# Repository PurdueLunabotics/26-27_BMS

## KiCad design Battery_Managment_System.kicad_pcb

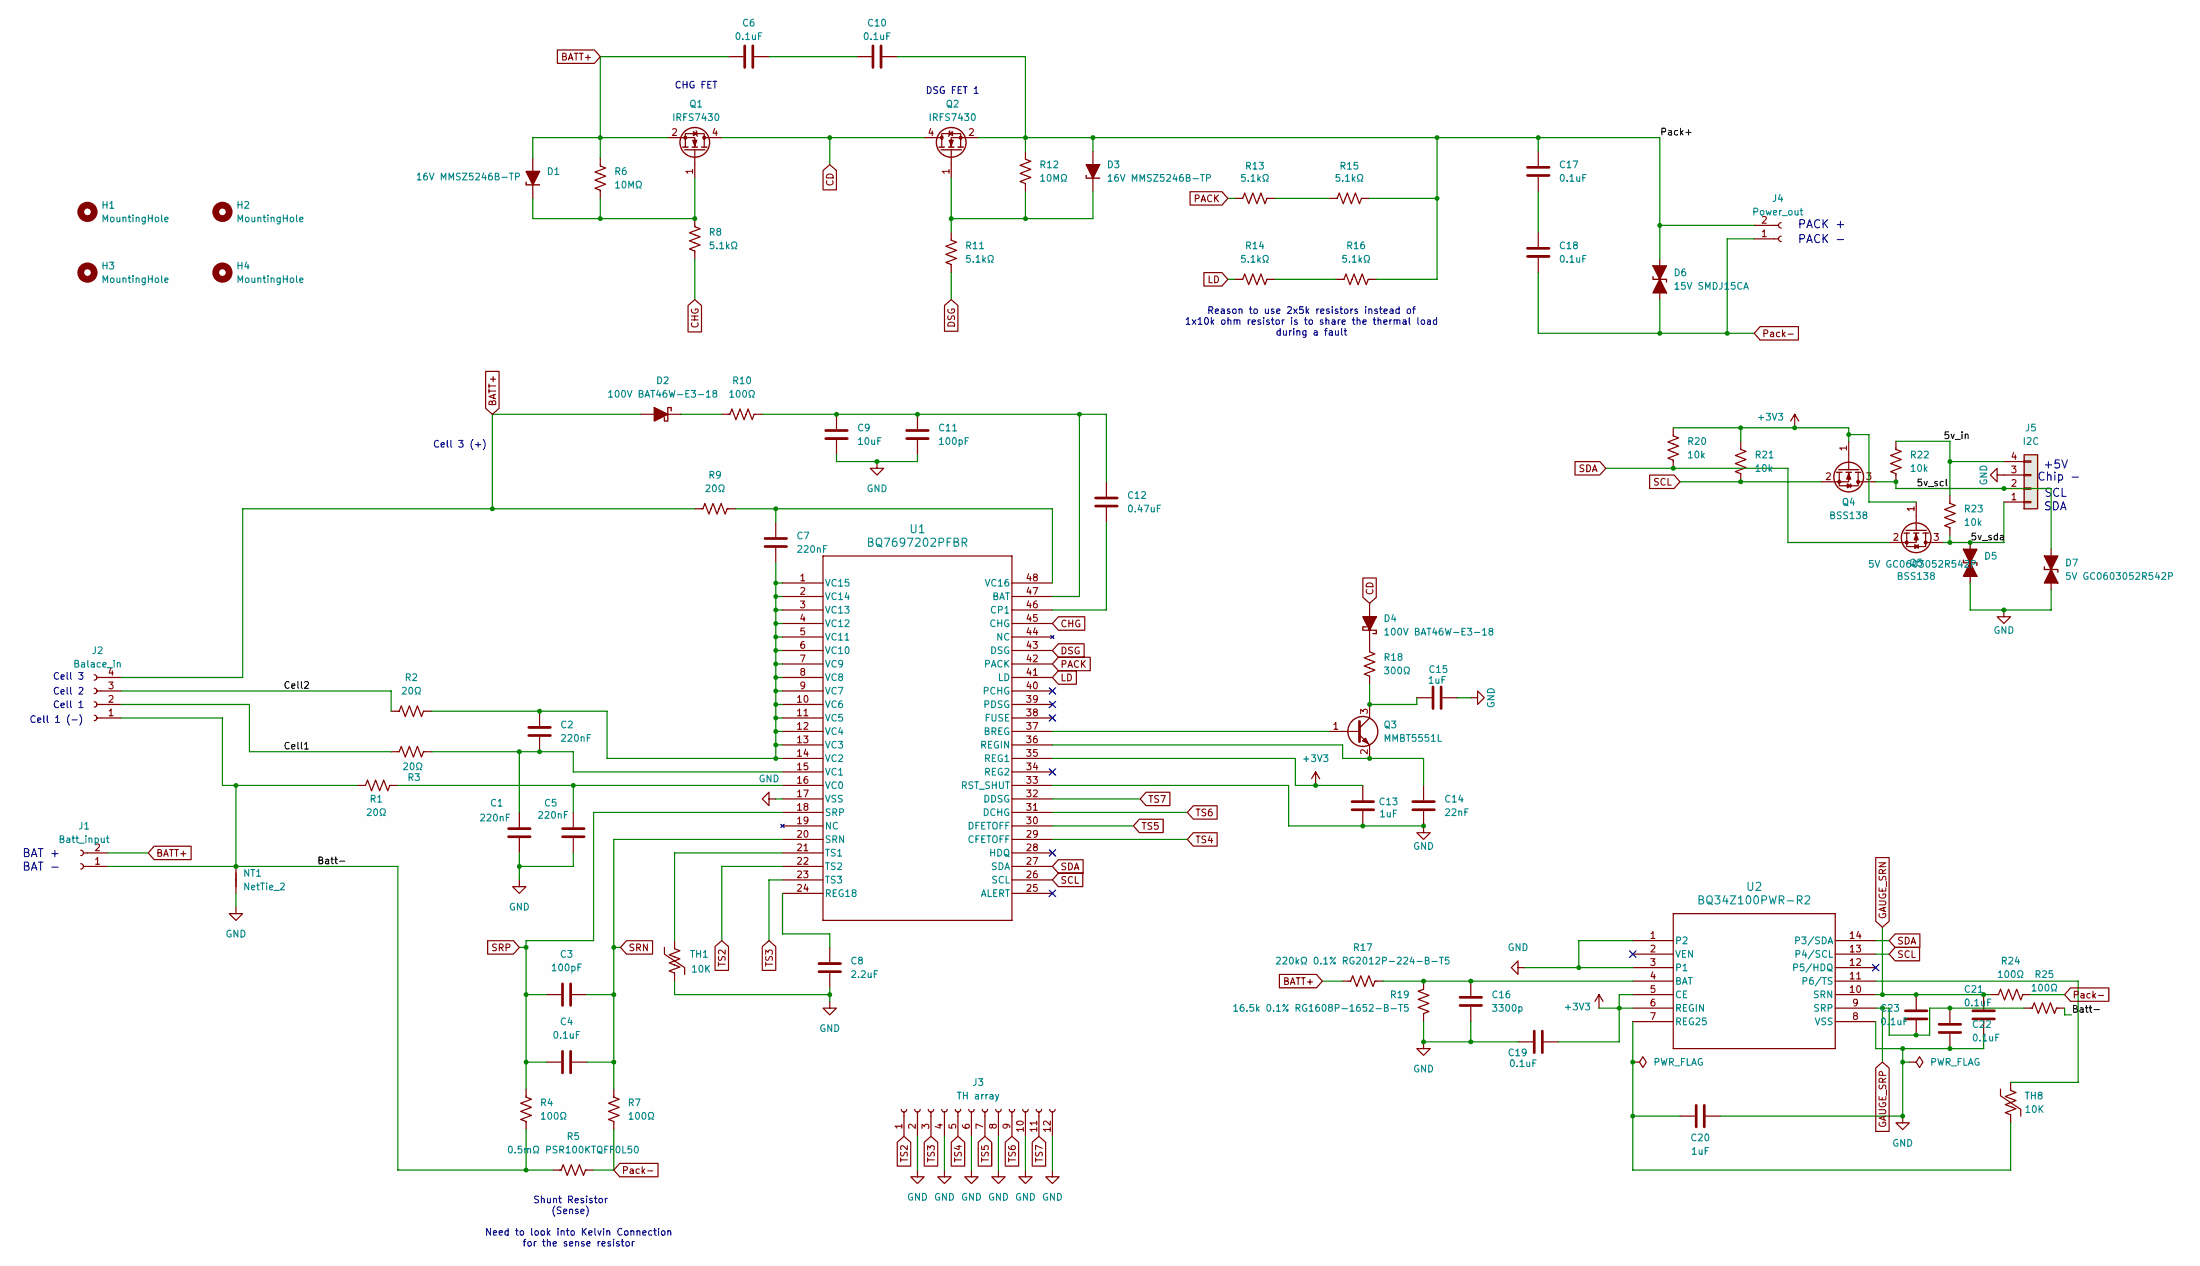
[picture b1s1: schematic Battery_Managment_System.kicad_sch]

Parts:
C1, C2, C5, C7: 220nF; C_0603_1608Metric; MPN CL10B224KB8NNNC
C3, C11: 100pF; C_0603_1608Metric; MPN C0603C101J1GACTU
C4, C6, C10, C17, C18, C21, C22, C23: 0.1uF; C_0805_2012Metric; MPN C2012X7R2A104K125AA
C8: 2.2uF; C_0603_1608Metric; MPN GRT188R61H225KE13D
C9: 10uF; C_0805_2012Metric; MPN GMC21X5R106K35NT
C12: 0.47uF; C_0603_1608Metric; MPN UMK107B7474KA-TR
C13, C15: 1uF; C_0603_1608Metric; MPN GRM188R71E105KA12D
C14: 22nF; C_0603_1608Metric; MPN CGA3E2X7R1H223K080AA
C16: 3300p; C_0603_1608Metric; MPN CL10B332KB8NNNC
C19: 0.1uF; C_0805_2012Metric; Voltage 10V; MPN C2012X7R2A104K125AA
C20: 1uF; C_0603_1608Metric; Voltage 10V; MPN GRM188R71E105KA12D
D1, D3: 16V MMSZ5246B-TP; D_SOD-123; MPN MMSZ5246B-TP
D2, D4: 100V BAT46W-E3-18; D_SOD-123; MPN BAT46W-E3-18
D5, D7: 5V GC0603052R542P; D_0603_1608Metric; MPN GC0603052R542P
D6: 15V SMDJ15CA; D_SMC; MPN SMDJ15CA
H1, H2, H3, H4: MountingHole; MountingHole_2.2mm_M2_DIN965_Pad_TopBottom
J1: Batt_input; TH_XT90PB-F; MPN XT90PB-M
J2: Balace_in; JST_XH_B4B-XH-A_1x04_P2.50mm_Vertical; MPN B4B-XH-A
J3: TH array; JST_XH_B12B-XH-A_1x12_P2.50mm_Vertical; MPN B12B-XH-A
J4: Power_out; XT90PWF; MPN XT90PW-F
J5: I2C; JST_XH_B4B-XH-A_1x04_P2.50mm_Vertical; MPN B4B-XH-A
NT1: NetTie_2; NetTie-2_SMD_Pad2.0mm
Q1, Q2: IRFS7430; TO-263-6; MPN IRFS7430TRL7PP
Q3: MMBT5551L; SOT-23; MPN MMBT5551L
Q4, Q5: BSS138; SOT-23; MPN BSS138-D
R1, R2, R3, R9: 20Ω; R_0603_1608Metric; MPN RCS060320R0FKEA
R4, R7, R10, R24, R25: 100Ω; R_0603_1608Metric; MPN SG73P1JTTD1000F
R5: 0.5mΩ PSR100KTQFF0L50; R_2512_6332Metric; MPN PSR100KTQFF0L50
R6, R12: 10MΩ; R_0603_1608Metric; MPN RCS060310M0FKEA
R8, R11, R13, R14, R15, R16: 5.1kΩ; R_0603_1608Metric; MPN RCS06035K10FKEA
R17: 220kΩ 0.1% RG2012P-224-B-T5; R_0805_2012Metric; Tolerance 0.1% 25ppm; MPN RG2012P-224-B-T5
R18: 300Ω; R_0603_1608Metric; MPN RCS0603300RFKEA
R19: 16.5k 0.1% RG1608P-1652-B-T5; R_0603_1608Metric; Tolerance 0.1% 25ppm; MPN RG1608P-1652-B-T5
R20, R21, R22, R23: 10k; R_0603_1608Metric; MPN SG73P1JTTD1002F
TH1, TH8: 10K; C_Disc_D3.0mm_W1.6mm_P2.50mm; MPN 103AT-2
U1: BQ7697202PFBR; TQFP-48_7x7mm_P0.5mm; MPN BQ7697202PFBR
U2: BQ34Z100PWR-R2; TSSOP-14_4.4x5mm_P0.65mm; MPN BQ34Z100PWR-R2

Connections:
+3V3: C13.1, C19.1, Q4.1 (G), Q5.1 (G), R20.2, R21.2, U1.35 (REG1), U2.5 (CE), U2.6 (REGIN)
/5v_in: J5.4, R22.2, R23.2
/5v_scl: D7.2 (A2), J5.2, Q4.3 (D), R22.1
/5v_sda: D5.2 (A2), J5.1, Q5.3 (D), R23.1
/Batt-: J1.1, J2.1, NT1.2, R1.2, R4.2, R5.1, R25.2
/Cell1: J2.2, R3.1
/Cell2: J2.3, R2.1
/Pack+: C10.2, C17.1, D3.2 (A), D6.2 (A2), J4.2, Q2.2 (S), Q2.3 (S), Q2.5 (S), Q2.6 (S), Q2.7 (S), R12.1, R15.2, R16.2
BATT+: C6.1, D1.2 (A), D2.2 (A), J1.2, J2.4, Q1.2 (S), Q1.3 (S), Q1.5 (S), Q1.6 (S), Q1.7 (S), R6.1, R9.1, R17.1
CD: D4.2 (A), Q1.4 (D), Q2.4 (D)
CHG: R8.2, U1.45 (CHG)
DSG: R11.2, U1.43 (DSG)
GAUGE_SRN: C21.2, C23.2, R24.1, U2.10 (SRN)
GAUGE_SRP: C22.2, C23.1, R25.1, U2.9 (SRP)
GND: C1.1, C5.1, C8.2, C9.2, C11.2, C13.2, C14.2, C15.2, C16.2, C19.2, C20.2, C21.1, C22.1, D5.1 (A1), D7.1 (A1), J3.2, J3.4, J3.6, J3.8, J3.10, J3.12, J5.3, NT1.1, R19.2, TH1.2, U1.17 (VSS), U1.33 (RST_SHUT), U2.1 (P2), U2.3 (P1), U2.8 (VSS)
LD: R14.1, U1.41 (LD)
unnamed: C6.2, C10.1
unnamed: C17.2, C18.1
unnamed: D1.1 (K), Q1.1 (G), R6.2, R8.1
unnamed: D2.1 (K), R10.1
unnamed: D3.1 (K), Q2.1 (G), R11.1, R12.2
unnamed: D4.1 (K), R18.2
unnamed: Q3.1 (B), U1.37 (BREG)
unnamed: C15.1, Q3.3 (C), R18.1
unnamed: C14.1, Q3.2 (E), U1.36 (REGIN)
unnamed: R13.2, R15.1
unnamed: R14.2, R16.1
unnamed: C9.1, C11.1, C12.1, R10.2, U1.47 (BAT)
unnamed: C12.2, U1.46 (CP1)
unnamed: C8.1, U1.24 (REG18)
unnamed: TH1.1, U1.21 (TS1)
unnamed: C5.2, R1.1, U1.16 (VC0)
unnamed: C1.2, C2.2, R3.2, U1.15 (VC1)
unnamed: C2.1, C7.1, R2.2, U1.1 (VC15), U1.2 (VC14), U1.3 (VC13), U1.4 (VC12), U1.5 (VC11), U1.6 (VC10), U1.7 (VC9), U1.8 (VC8), U1.9 (VC7), U1.10 (VC6), U1.11 (VC5), U1.12 (VC4), U1.13 (VC3), U1.14 (VC2)
unnamed: C7.2, R9.2, U1.48 (VC16)
unnamed: C16.1, R17.2, R19.1, U2.4 (BAT)
unnamed: TH8.2, U2.11 (P6/TS)
unnamed: C20.1, TH8.1, U2.7 (REG25)
PACK: R13.1, U1.42 (PACK)
Pack-: C18.2, D6.1 (A1), J4.1, R5.2, R7.2, R24.2
SCL: Q4.2 (S), R21.1, U1.26 (SCL), U2.13 (P4/SCL)
SDA: Q5.2 (S), R20.1, U1.27 (SDA), U2.14 (P3/SDA)
SRN: C3.2, C4.2, R7.1, U1.20 (SRN)
SRP: C3.1, C4.1, R4.1, U1.18 (SRP)
TS2: J3.1, U1.22 (TS2)
TS3: J3.3, U1.23 (TS3)
TS4: J3.5, U1.29 (CFETOFF)
TS5: J3.7, U1.30 (DFETOFF)
TS6: J3.9, U1.31 (DCHG)
TS7: J3.11, U1.32 (DDSG)

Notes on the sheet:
Reason to use 2x5k resistors instead of 1x10k ohm resistor is to share the thermal load during a fault
PACK -
Need to look into Kelvin Connection for the sense resistor
DSG FET 1
Chip -
CHG FET
Cell 1
BAT +
Cell 3 (+)
+5V
BAT -
PACK +
Shunt Resistor (Sense)
Cell 2
Cell 1 (-)
Cell 3
SCL
SDA

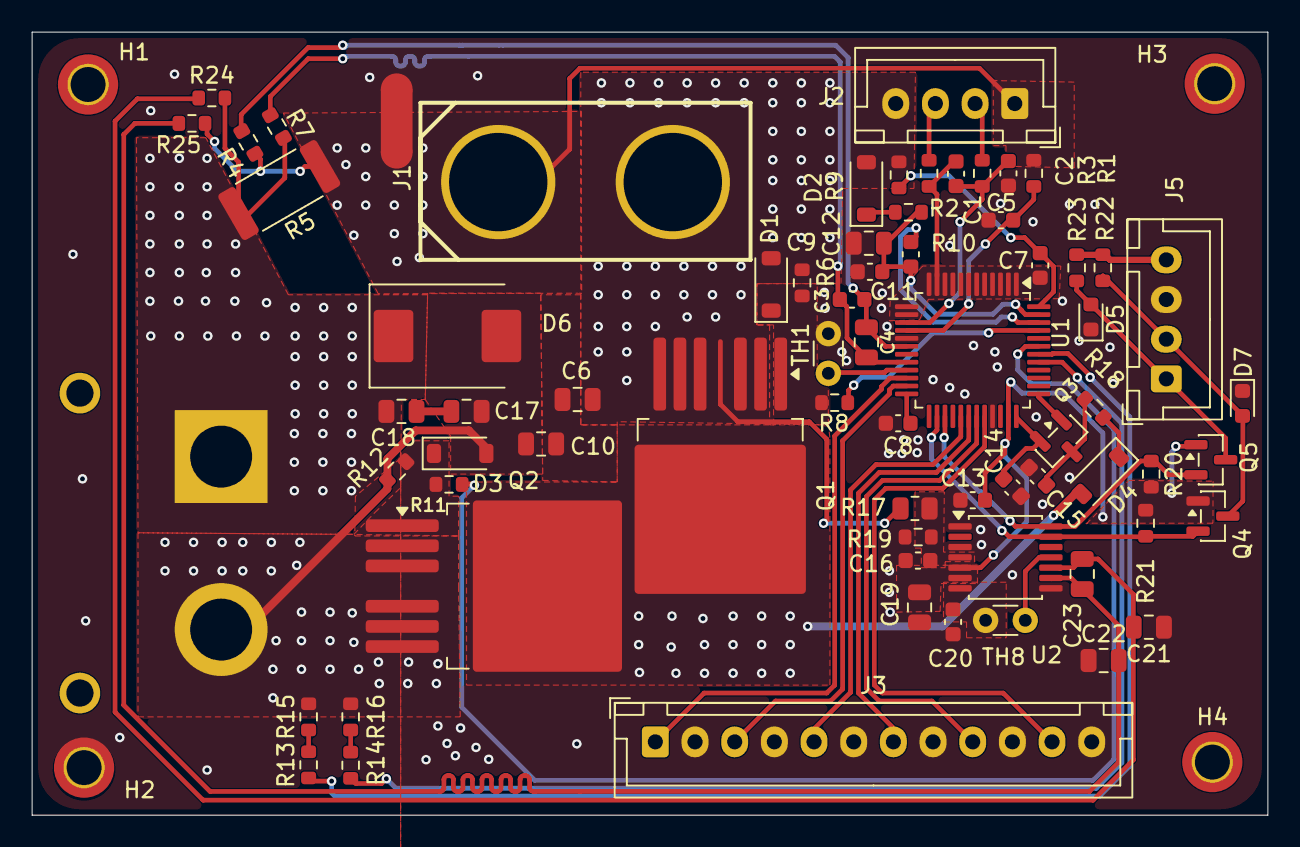
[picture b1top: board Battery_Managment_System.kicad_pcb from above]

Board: 2 copper layers, 77.9 x 49.4 mm, 74 parts (1 on the bottom side), 50 nets.

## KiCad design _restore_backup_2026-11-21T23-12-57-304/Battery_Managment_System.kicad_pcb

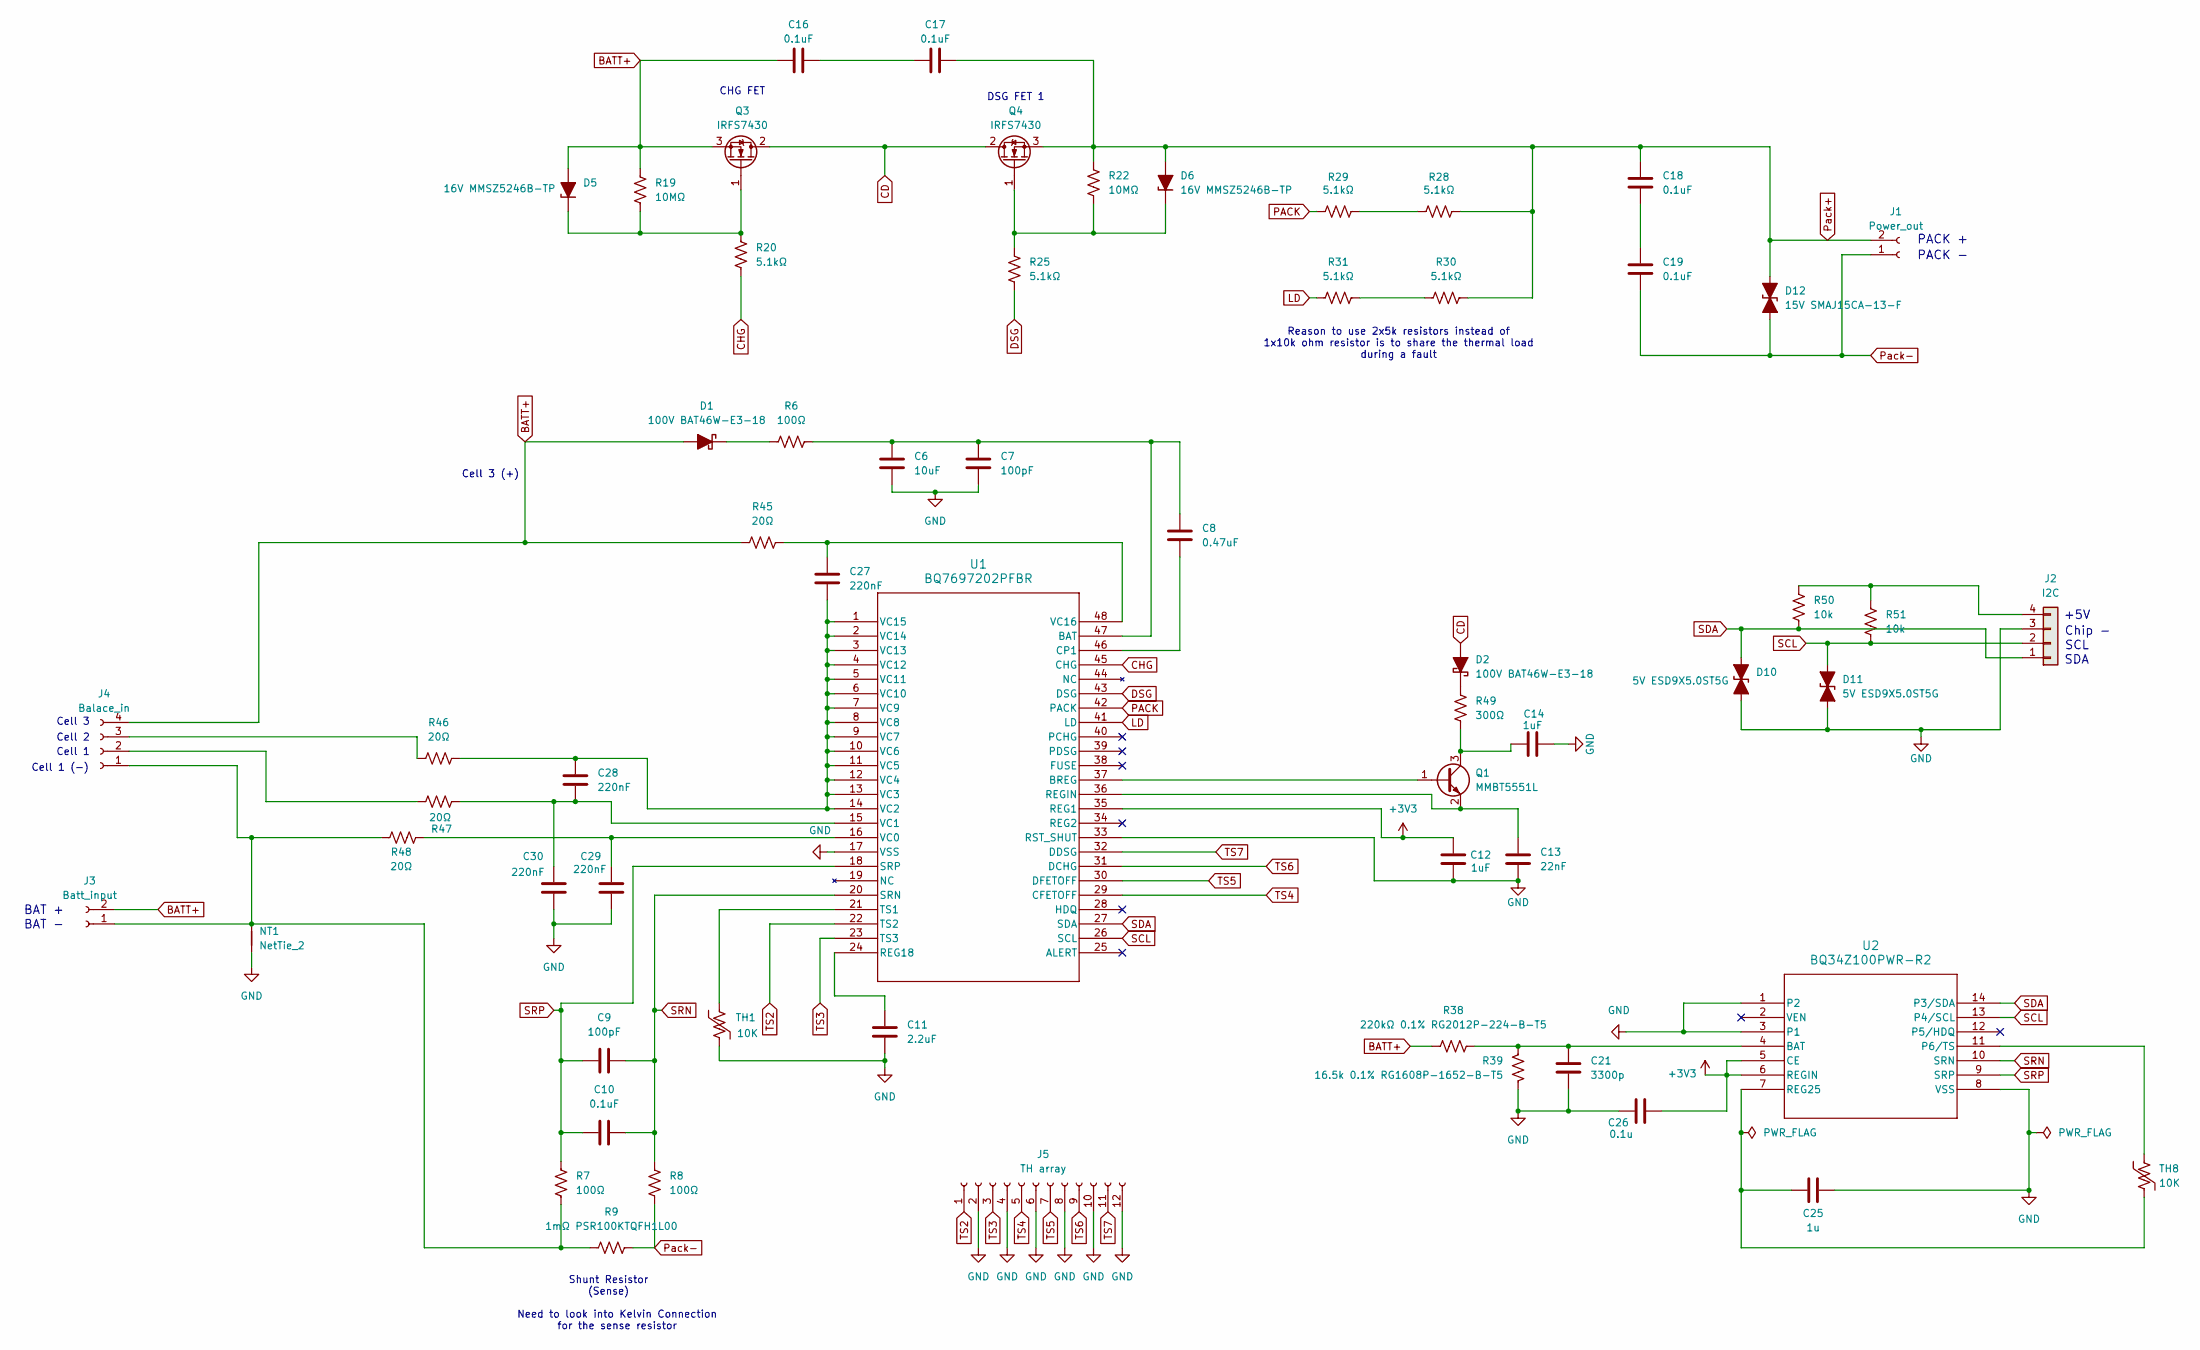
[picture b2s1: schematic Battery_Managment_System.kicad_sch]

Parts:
C6: 10uF; C_0805_2012Metric
C7, C9: 100pF; C_0402_1005Metric
C8: 0.47uF; C_0402_1005Metric
C10: 0.1uF; C_0402_1005Metric
C11: 2.2uF; C_0603_1608Metric
C12, C14: 1uF; C_0603_1608Metric
C13: 22nF; C_0402_1005Metric
C16, C17, C18, C19: 0.1uF; C_0805_2012Metric
C21: 3300p; C_0402_1005Metric
C25: 1u; C_0603_1608Metric; Voltage 10V
C26: 0.1u; C_0402_1005Metric; Voltage 10V
C27, C28, C29, C30: 220nF; C_0402_1005Metric
D1, D2: 100V BAT46W-E3-18; D_SOD-123
D5, D6: 16V MMSZ5246B-TP; D_SOD-123
D10, D11: 5V ESD9X5.0ST5G; D_SOD-923
D12: 15V SMAJ15CA-13-F; D_SMA
J1: Power_out; XT90PWF
J2: I2C; JST_XH_B4B-XH-A_1x04_P2.50mm_Vertical
J3: Batt_input; TH_XT90PB-F
J4: Balace_in; JST_XH_B4B-XH-A_1x04_P2.50mm_Vertical
J5: TH array; JST_XH_B12B-XH-A_1x12_P2.50mm_Vertical
NT1: NetTie_2; NetTie-2_SMD_Pad2.0mm
Q1: MMBT5551L; SOT-23
Q3, Q4: IRFS7430; TO-263-2
R6, R7, R8: 100Ω; R_0402_1005Metric
R9: 1mΩ PSR100KTQFH1L00; R_2512_6332Metric
R19, R22: 10MΩ; R_0402_1005Metric
R20, R25, R28, R29, R30, R31: 5.1kΩ; R_0402_1005Metric
R38: 220kΩ 0.1% RG2012P-224-B-T5; R_0805_2012Metric; Tolerance 0.1% 25ppm
R39: 16.5k 0.1% RG1608P-1652-B-T5; R_0603_1608Metric; Tolerance 0.1% 25ppm
R45, R46, R47, R48: 20Ω; R_0402_1005Metric
R49: 300Ω; R_0402_1005Metric
R50, R51: 10k; R_0402_1005Metric
TH1: 10K; C_Disc_D3.0mm_W1.6mm_P2.50mm
TH8: 10K; C_Disc_D3.0mm_W1.6mm_P2.50mm; MPN Semitec 103AT-2
U1: BQ7697202PFBR; TQFP-48_7x7mm_P0.5mm
U2: BQ34Z100PWR-R2; TSSOP-14_4.4x5mm_P0.65mm; MPN BQ34Z100PWR-R2

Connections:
+3V3: C12.1, C26.1, U1.35 (REG1), U2.5 (CE), U2.6 (REGIN)
BATT+: C16.1, D1.2 (A), D5.2 (A), J3.2, J4.4, Q3.3 (S), R19.1, R38.1, R45.1
CD: D2.2 (A), Q3.2 (D), Q4.2 (D)
CHG: R20.2, U1.45 (CHG)
DSG: R25.2, U1.43 (DSG)
GND: C6.2, C7.2, C11.2, C12.2, C13.2, C14.2, C21.2, C25.2, C26.2, C29.1, C30.1, D10.1 (A1), D11.1 (A1), J2.3, J5.2, J5.4, J5.6, J5.8, J5.10, J5.12, NT1.1, R39.2, TH1.2, U1.17 (VSS), U1.33 (RST_SHUT), U2.1 (P2), U2.3 (P1), U2.8 (VSS)
LD: R31.1, U1.41 (LD)
unnamed: C16.2, C17.1
unnamed: C18.2, C19.1
unnamed: D1.1 (K), R6.1
unnamed: D2.1 (K), R49.2
unnamed: D5.1 (K), Q3.1 (G), R19.2, R20.1
unnamed: D6.1 (K), Q4.1 (G), R22.2, R25.1
unnamed: J2.4, R50.2, R51.2
unnamed: J3.1, J4.1, NT1.2, R7.2, R9.1, R48.2
unnamed: J4.2, R47.1
unnamed: J4.3, R46.1
unnamed: Q1.1 (B), U1.37 (BREG)
unnamed: C14.1, Q1.3 (C), R49.1
unnamed: C13.1, Q1.2 (E), U1.36 (REGIN)
unnamed: R28.1, R29.2
unnamed: R30.1, R31.2
unnamed: C6.1, C7.1, C8.1, R6.2, U1.47 (BAT)
unnamed: C8.2, U1.46 (CP1)
unnamed: C11.1, U1.24 (REG18)
unnamed: TH1.1, U1.21 (TS1)
unnamed: C29.2, R48.1, U1.16 (VC0)
unnamed: C28.2, C30.2, R47.2, U1.15 (VC1)
unnamed: C27.1, C28.1, R46.2, U1.1 (VC15), U1.2 (VC14), U1.3 (VC13), U1.4 (VC12), U1.5 (VC11), U1.6 (VC10), U1.7 (VC9), U1.8 (VC8), U1.9 (VC7), U1.10 (VC6), U1.11 (VC5), U1.12 (VC4), U1.13 (VC3), U1.14 (VC2)
unnamed: C27.2, R45.2, U1.48 (VC16)
unnamed: C21.1, R38.2, R39.1, U2.4 (BAT)
unnamed: TH8.2, U2.11 (P6/TS)
unnamed: C25.1, TH8.1, U2.7 (REG25)
PACK: R29.1, U1.42 (PACK)
Pack+: C17.2, C18.1, D6.2 (A), D12.2 (A2), J1.2, Q4.3 (S), R22.1, R28.2, R30.2
Pack-: C19.2, D12.1 (A1), J1.1, R8.2, R9.2
SCL: D11.2 (A2), J2.2, R51.1, U1.26 (SCL), U2.13 (P4/SCL)
SDA: D10.2 (A2), J2.1, R50.1, U1.27 (SDA), U2.14 (P3/SDA)
SRN: C9.2, C10.2, R8.1, U1.20 (SRN), U2.10 (SRN)
SRP: C9.1, C10.1, R7.1, U1.18 (SRP), U2.9 (SRP)
TS2: J5.1, U1.22 (TS2)
TS3: J5.3, U1.23 (TS3)
TS4: J5.5, U1.29 (CFETOFF)
TS5: J5.7, U1.30 (DFETOFF)
TS6: J5.9, U1.31 (DCHG)
TS7: J5.11, U1.32 (DDSG)

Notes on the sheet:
Chip -
Reason to use 2x5k resistors instead of 1x10k ohm resistor is to share the thermal load during a fault
PACK -
+5V
Need to look into Kelvin Connection for the sense resistor
DSG FET 1
CHG FET
Cell 1
BAT +
Cell 3 (+)
BAT -
PACK +
Shunt Resistor (Sense)
Cell 2
Cell 1 (-)
Cell 3
SDA
SCL

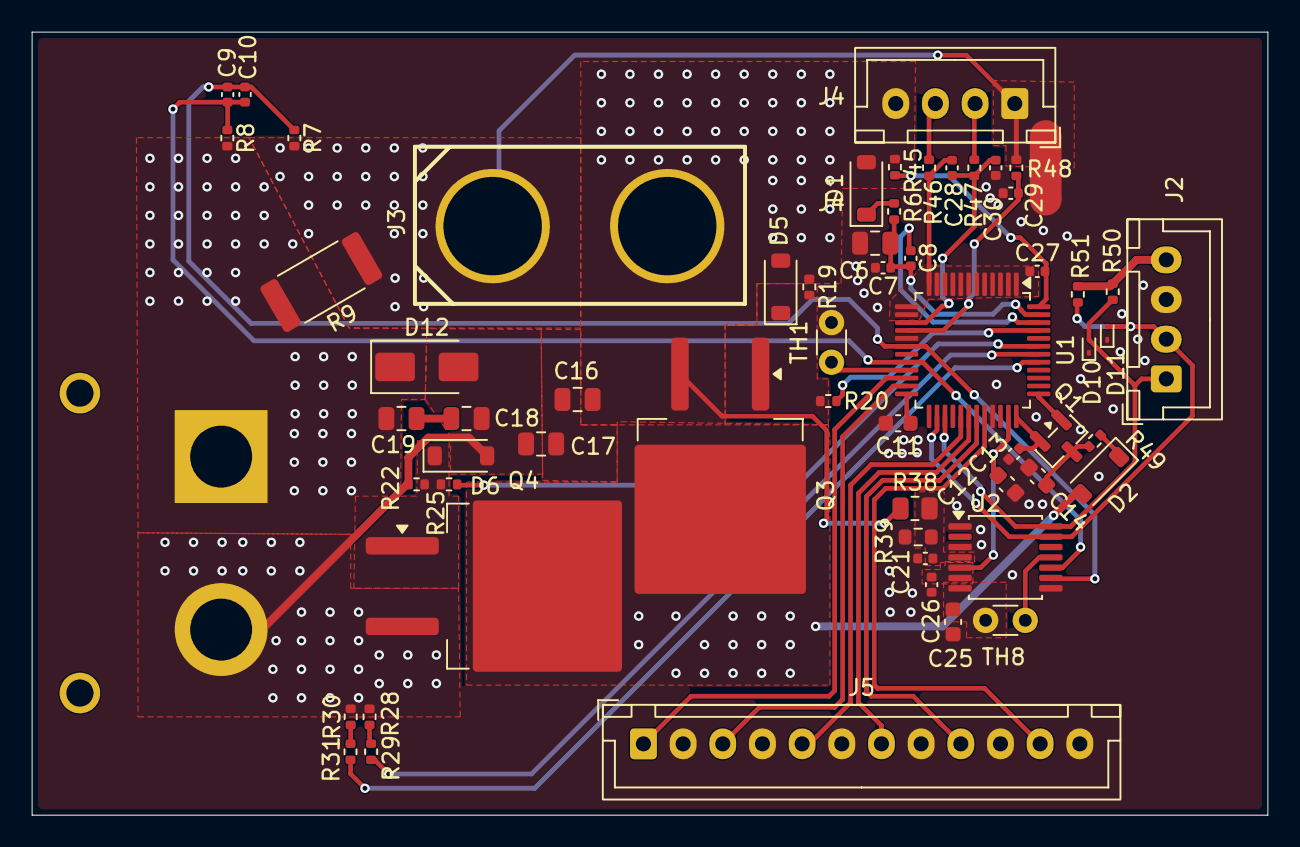
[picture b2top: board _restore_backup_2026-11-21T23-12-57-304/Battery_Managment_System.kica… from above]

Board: 2 copper layers, 77.9 x 49.4 mm, 61 parts (1 on the bottom side), 46 nets.
